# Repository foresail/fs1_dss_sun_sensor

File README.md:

# Foresail-1 DSS Sun Sensor

This repository contains the public available design files for the DSS sun sensor designed for the Foresail-1 Cubesat.

The performance and testing of this sensor has been documented in [this article](https://doi.org/10.1016/j.asr.2026.01.083).

The general characteristics of sensor design are:
- Dimensions: 20.4 mm × 24.8 mm × 7 mm
- Mass: 4.4 grams
- Panel mountedable into 14x14 mm hole with two M2 screws.
- Electrical connection by soldering on the panel PCB or by harness.
- FOV: ~30 degrees, resolution: 0.027°, accuracy: ±0.008°
- Refresh rate up to 38 Hz. (Sampling time: 15 ms + communication overhead)
- Can provide following data products:
    - Raw current measurements
    - Point & intensity measurements
    - Sun vector & intensity measurements
    - Angles & intensity measurements
- I2C digital serial interface (hardware version 4)
- RS-485 digital interface (hardware version 5)
- Low power consumption < 4 mW when active
- Nominal operating voltage: 3.6 - 3.8V: Can be extened easily to 2.0 – 5.5 V.

## Documentation

- [Research Paper](https://doi.org/10.1016/j.asr.2026.01.083)
- [FS1 ADCS DSS Sun Sensor Design Document](docs/FS1p_ADCS_DSS_Digital_Sun_Sensor_Hardware_Design.pdf)
- [Version 4 schematic (I2C variant)](v4/dss_v4_schema.pdf)
- [Version 4 firmware source code](v4/fw)
- [Version 5 schematic (RS-485 variant)](v5/dss_v5_schema.pdf)
- [Version 5 firmware source code](v5/fw)
- [Calibration and test tools for PC](calibration)
- [Mechanical design files](mechanical)

## Licence

The design is licenced under [CERN Open Hardware Licence Version 2](LICENCE)

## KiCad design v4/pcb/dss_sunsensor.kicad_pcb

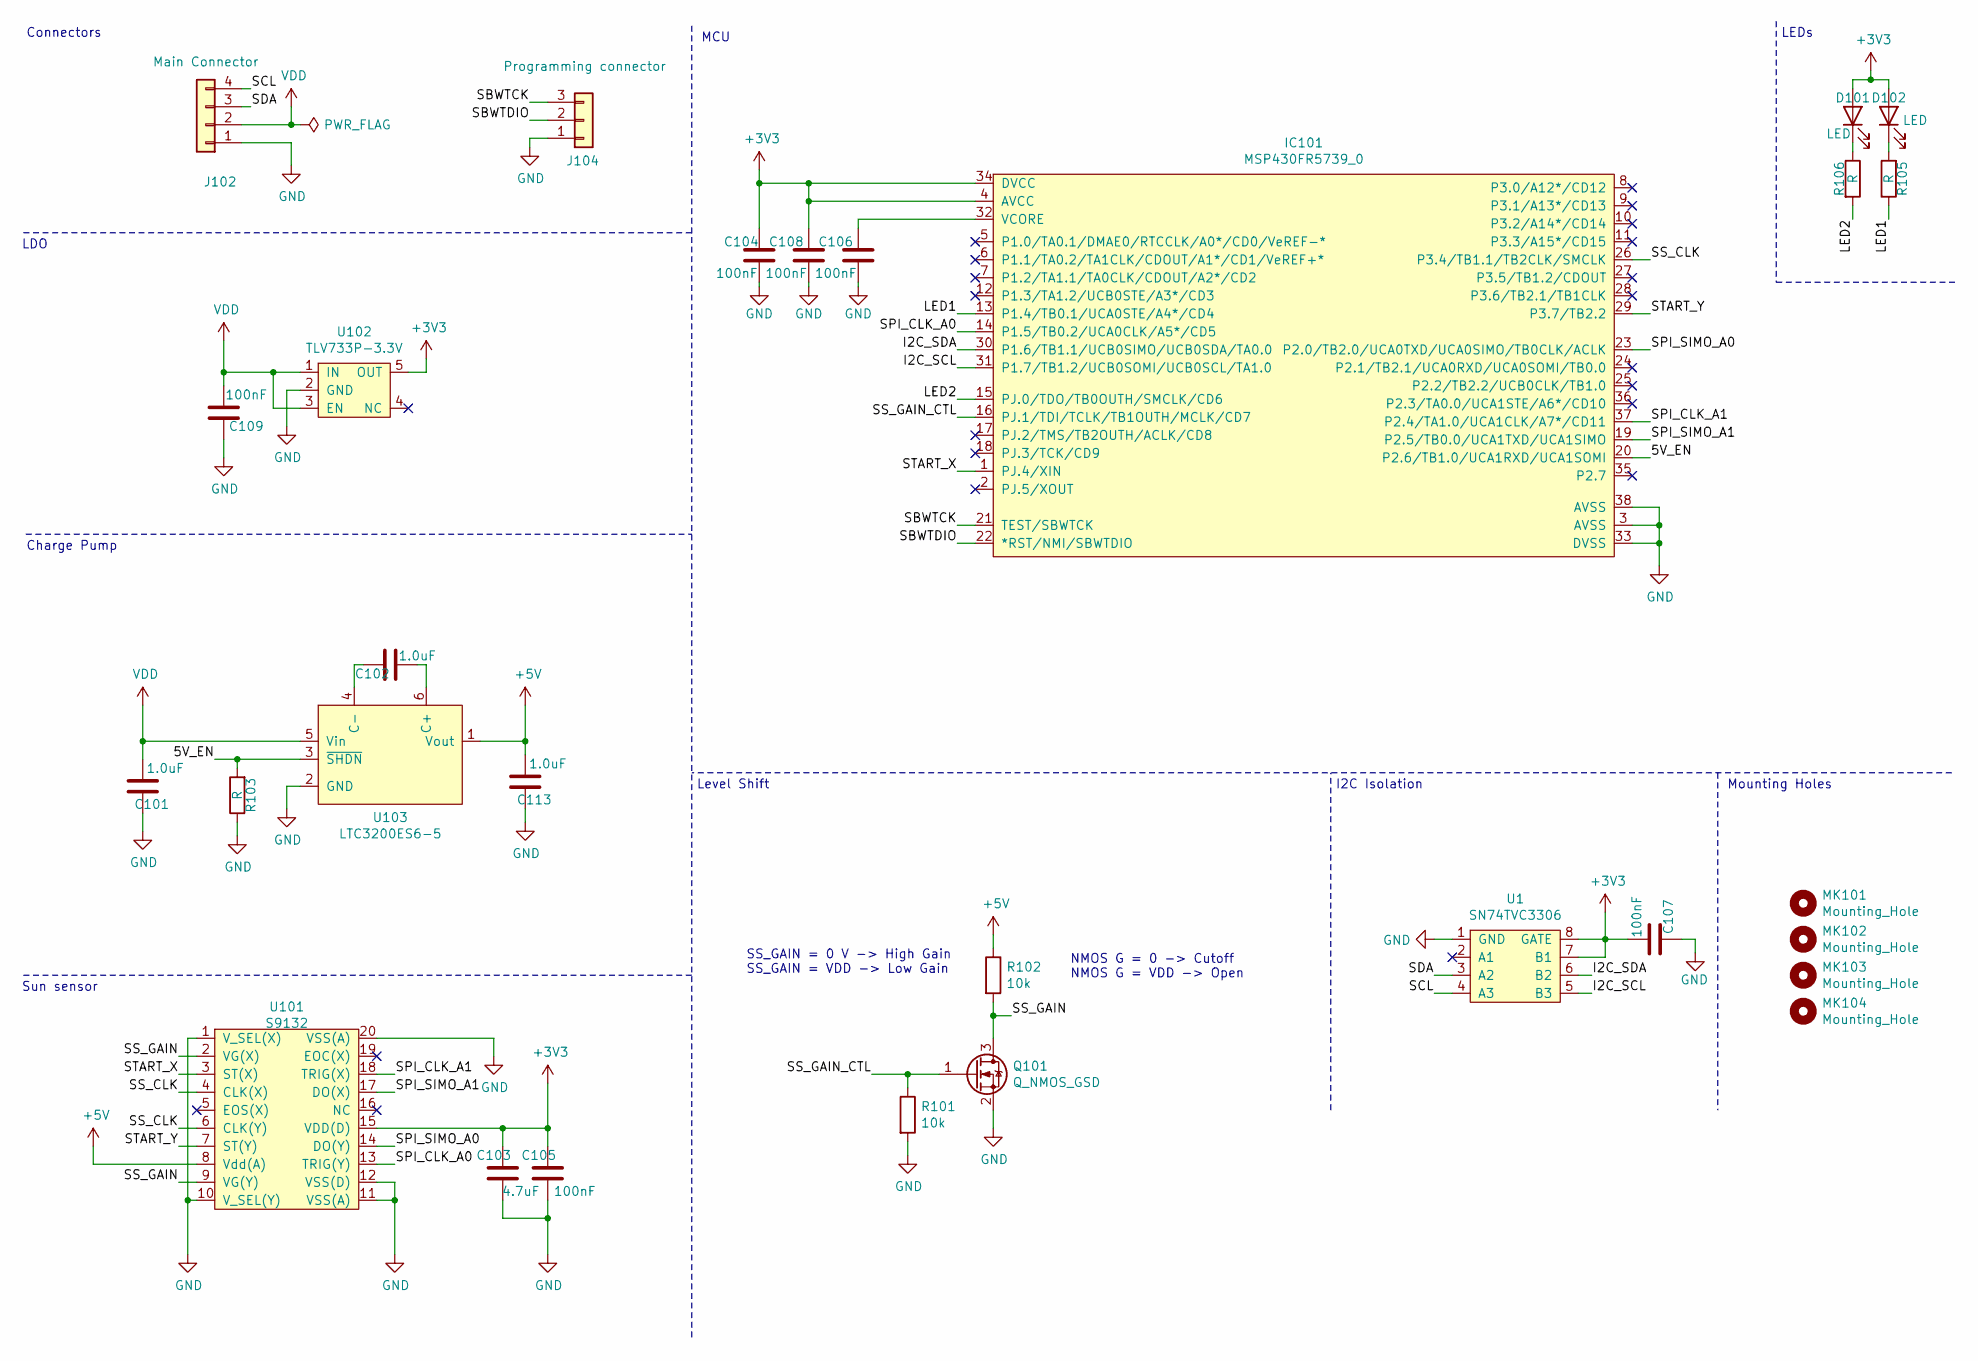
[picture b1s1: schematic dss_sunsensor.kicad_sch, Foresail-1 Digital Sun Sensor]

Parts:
C101, C102, C113: 1.0uF; C_0603_1608Metric
C103: 4.7uF; C_0603_1608Metric
C104, C105, C106, C107, C108, C109: 100nF; C_0402_1005Metric
D101, D102: LED; LED_0603_1608Metric
IC101: MSP430FR5739_0; TSSOP-38_6.1mm
J102: Main Connector; PinHeader_1x04_P1.27mm_Horizontal
J104: Programming connector; PinHeader_1x03_P1.27mm_Horizontal
MK101, MK102, MK103, MK104: Mounting_Hole; MountingHole_2.2mm_M2
Q101: Q_NMOS_GSD; SOT-23
R101, R102: 10k; R_0402_1005Metric
R103, R105, R106: R; R_0402_1005Metric
U1: SN74TVC3306; VSSOP-8_2.4x2.1mm_P0.5mm
U101: S9132
U102: TLV733P-3.3V; SOT-23-5
U103: LTC3200ES6-5; SOT-23-6

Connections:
+3V3: C103.2, C104.2, C105.2, C107.1, C108.2, D101.2 (A), D102.2 (A), IC101.4 (AVCC), IC101.34 (DVCC), U1.7 (B1), U1.8 (GATE), U101.15 (VDD(D)), U102.5 (OUT)
+5V: C113.1, R102.1, U101.8 (Vdd(A)), U103.1 (Vout)
/5V_EN: IC101.20 (P2.6/TB1.0/UCA1RXD/UCA1SOMI), R103.2, U103.3 (~SHDN)
/I2C_SCL: IC101.31 (P1.7/TB1.2/UCB0SOMI/UCB0SCL/TA1.0), U1.5 (B3)
/I2C_SDA: IC101.30 (P1.6/TB1.1/UCB0SIMO/UCB0SDA/TA0.0), U1.6 (B2)
/LED1: IC101.13 (P1.4/TB0.1/UCA0STE/A4*/CD4), R105.1
/LED2: IC101.15 (PJ.0/TDO/TB0OUTH/SMCLK/CD6), R106.2
/SBWTCK: IC101.21 (TEST/SBWTCK), J104.3
/SBWTDIO: IC101.22 (*RST/NMI/SBWTDIO), J104.2
/SCL: J102.4, U1.4 (A3)
/SDA: J102.3, U1.3 (A2)
/SPI_CLK_A0: IC101.14 (P1.5/TB0.2/UCA0CLK/A5*/CD5), U101.13 (TRIG(Y))
/SPI_CLK_A1: IC101.37 (P2.4/TA1.0/UCA1CLK/A7*/CD11), U101.18 (TRIG(X))
/SPI_SIMO_A0: IC101.23 (P2.0/TB2.0/UCA0TXD/UCA0SIMO/TB0CLK/ACLK), U101.14 (DO(Y))
/SPI_SIMO_A1: IC101.19 (P2.5/TB0.0/UCA1TXD/UCA1SIMO), U101.17 (DO(X))
/SS_CLK: IC101.26 (P3.4/TB1.1/TB2CLK/SMCLK), U101.4 (CLK(X)), U101.6 (CLK(Y))
/SS_GAIN: Q101.3 (D), R102.2, U101.2 (VG(X)), U101.9 (VG(Y))
/SS_GAIN_CTL: IC101.16 (PJ.1/TDI/TCLK/TB1OUTH/MCLK/CD7), Q101.1 (G), R101.1
/START_X: IC101.1 (PJ.4/XIN), U101.3 (ST(X))
/START_Y: IC101.29 (P3.7/TB2.2), U101.7 (ST(Y))
GND: C101.2, C103.1, C104.1, C105.1, C106.1, C107.2, C108.1, C109.2, C113.2, IC101.3 (AVSS), IC101.33 (DVSS), IC101.38 (AVSS), J102.1, J104.1, Q101.2 (S), R101.2, R103.1, U1.1 (GND), U101.1 (V_SEL(X)), U101.10 (V_SEL(Y)), U101.11 (VSS(A)), U101.12 (VSS(D)), U101.20 (VSS(A)), U102.2 (GND), U103.2 (GND)
unnamed: C102.1, U103.6 (C+)
unnamed: C102.2, U103.4 (C-)
unnamed: C106.2, IC101.32 (VCORE)
unnamed: D101.1 (K), R106.1
unnamed: D102.1 (K), R105.2
VDD: C101.1, C109.1, J102.2, U102.1 (IN), U102.3 (EN), U103.5 (Vin)

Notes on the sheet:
LDO
Mounting Holes
SS_GAIN = 0 V -> High Gain SS_GAIN = VDD -> Low Gain
Charge Pump
Sun sensor
NMOS G = 0 -> Cutoff NMOS G = VDD -> Open
Connectors
Level Shift
LEDs
MCU
I2C Isolation

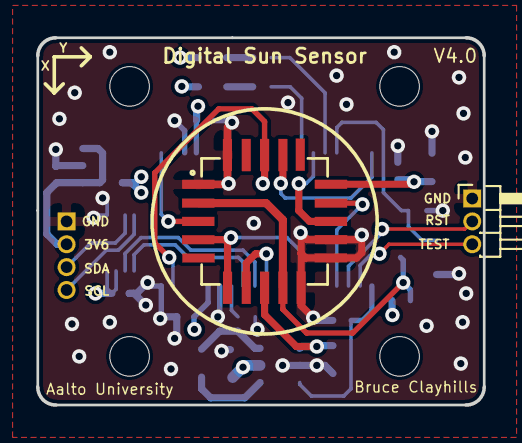
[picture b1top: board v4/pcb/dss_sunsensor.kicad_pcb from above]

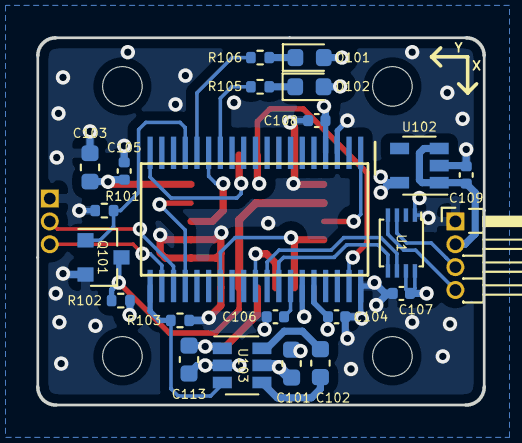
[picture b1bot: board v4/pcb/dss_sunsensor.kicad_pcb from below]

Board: 4 copper layers, 24.8 x 20.4 mm, 29 parts (23 on the bottom side), 27 nets.

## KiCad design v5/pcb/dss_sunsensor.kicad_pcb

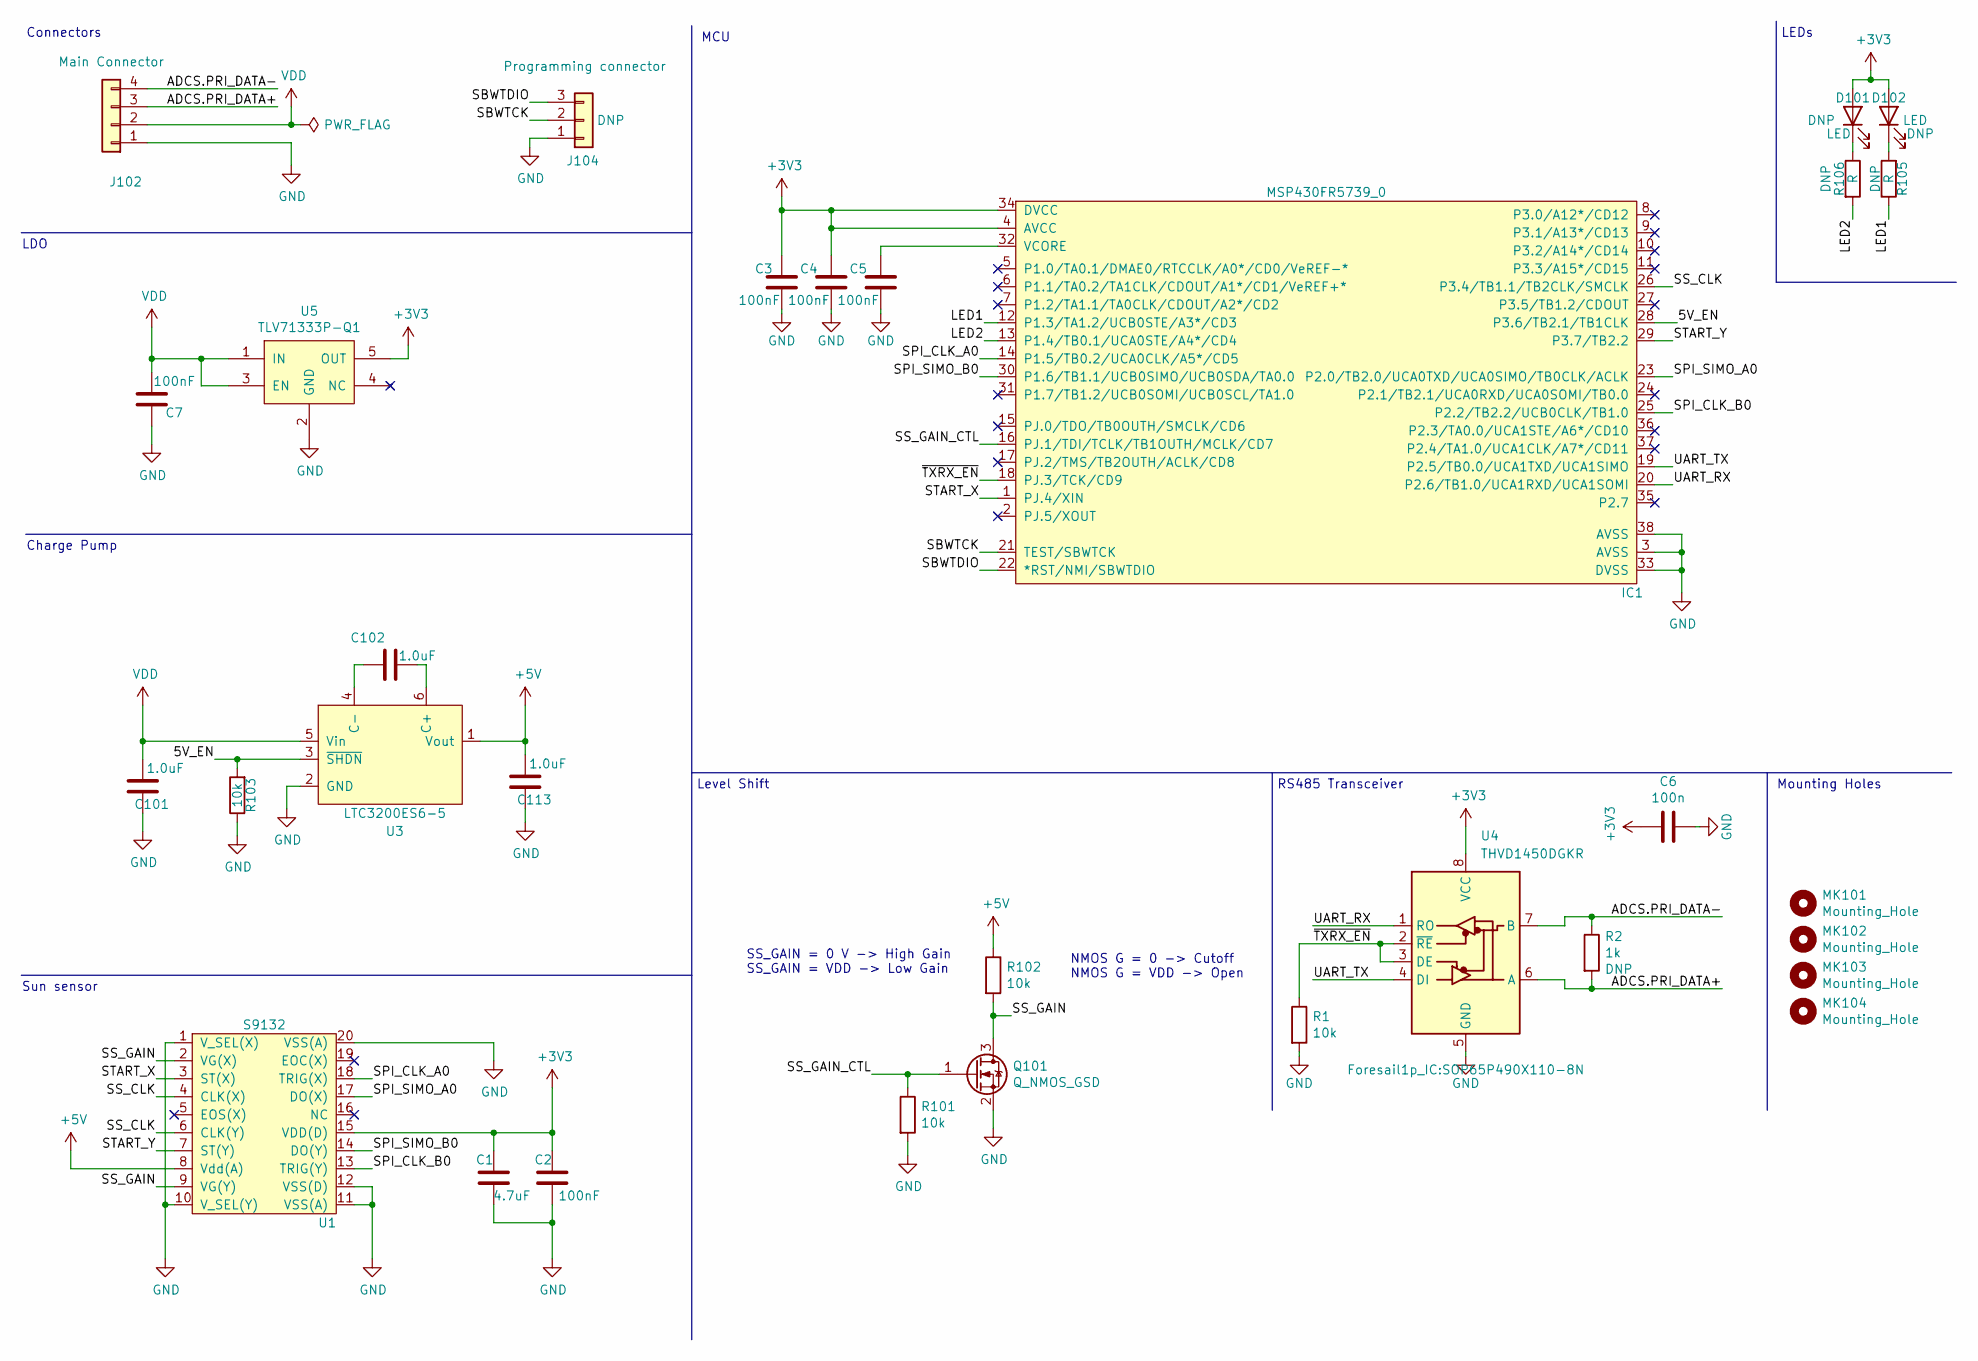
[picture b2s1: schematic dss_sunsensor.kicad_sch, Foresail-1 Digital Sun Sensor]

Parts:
C1: 4.7uF; C_0603_1608Metric
C2, C3, C4, C5, C7: 100nF; C_0402_1005Metric
C6: 100n; C_0402_1005Metric
C101, C102, C113: 1.0uF; C_0603_1608Metric
D101, D102: LED; LED_0603_1608Metric
IC1: MSP430FR5739_0; TSSOP-38_6.1mm
J102: Main Connector; PinHeader_1x04_P1.27mm_Horizontal
J104: Programming connector; PinHeader_1x03_P1.27mm_Horizontal
MK101, MK102, MK103, MK104: Mounting_Hole; MountingHole_2.2mm_M2
Q101: Q_NMOS_GSD; SOT-23
R1, R101, R102, R103: 10k; R_0402_1005Metric
R2: 1k; R_0402_1005Metric
R105, R106: R; R_0402_1005Metric
U1: S9132
U3: LTC3200ES6-5; SOT-23-6
U4: THVD1450DGKR; SOP65P490X110-8N
U5: TLV71333P-Q1; SOT-23-5; Mouser 595-TLV71333PQDBVRQ1

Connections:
+3V3: C1.2, C2.2, C3.2, C4.2, C6.1, D101.2 (A), D102.2 (A), IC1.4 (AVCC), IC1.34 (DVCC), U1.15 (VDD(D)), U4.8 (VCC), U5.5 (OUT); also elsewhere on the board
+5V: C113.1, R102.1, U1.8 (Vdd(A)), U3.1 (Vout)
/5V_EN: IC1.28 (P3.6/TB2.1/TB1CLK), R103.2, U3.3 (~SHDN)
/ADCS.PRI_DATA+: J102.3, R2.2, U4.6 (A)
/ADCS.PRI_DATA-: J102.4, R2.1, U4.7 (B)
/LED1: IC1.12 (P1.3/TA1.2/UCB0STE/A3*/CD3), R105.1
/LED2: IC1.13 (P1.4/TB0.1/UCA0STE/A4*/CD4), R106.2
/SBWTCK: IC1.21 (TEST/SBWTCK), J104.2
/SBWTDIO: IC1.22 (*RST/NMI/SBWTDIO), J104.3
/SPI_CLK_A0: IC1.14 (P1.5/TB0.2/UCA0CLK/A5*/CD5), U1.18 (TRIG(X))
/SPI_CLK_B0: IC1.25 (P2.2/TB2.2/UCB0CLK/TB1.0), U1.13 (TRIG(Y))
/SPI_SIMO_A0: IC1.23 (P2.0/TB2.0/UCA0TXD/UCA0SIMO/TB0CLK/ACLK), U1.17 (DO(X))
/SPI_SIMO_B0: IC1.30 (P1.6/TB1.1/UCB0SIMO/UCB0SDA/TA0.0), U1.14 (DO(Y))
/SS_CLK: IC1.26 (P3.4/TB1.1/TB2CLK/SMCLK), U1.4 (CLK(X)), U1.6 (CLK(Y))
/SS_GAIN: Q101.3 (D), R102.2, U1.2 (VG(X)), U1.9 (VG(Y))
/SS_GAIN_CTL: IC1.16 (PJ.1/TDI/TCLK/TB1OUTH/MCLK/CD7), Q101.1 (G), R101.1
/START_X: IC1.1 (PJ.4/XIN), U1.3 (ST(X))
/START_Y: IC1.29 (P3.7/TB2.2), U1.7 (ST(Y))
/UART_RX: IC1.20 (P2.6/TB1.0/UCA1RXD/UCA1SOMI), U4.1 (RO)
/UART_TX: IC1.19 (P2.5/TB0.0/UCA1TXD/UCA1SIMO), U4.4 (DI)
/~TXRX_EN: IC1.18 (PJ.3/TCK/CD9), R1.1, U4.2 (~RE), U4.3 (DE)
GND: C1.1, C2.1, C3.1, C4.1, C5.1, C6.2, C7.2, C101.2, C113.2, IC1.3 (AVSS), IC1.33 (DVSS), IC1.38 (AVSS), J102.1, J104.1, Q101.2 (S), R1.2, R101.2, R103.1, U1.1 (V_SEL(X)), U1.10 (V_SEL(Y)), U1.11 (VSS(A)), U1.12 (VSS(D)), U1.20 (VSS(A)), U3.2 (GND), U4.5 (GND), U5.2 (GND); also elsewhere on the board
unnamed: D101.1 (K), R106.1
unnamed: D102.1 (K), R105.2
unnamed: C5.2, IC1.32 (VCORE)
unnamed: C102.1, U3.6 (C+)
unnamed: C102.2, U3.4 (C-)
VDD: C7.1, C101.1, J102.2, U3.5 (Vin), U5.1 (IN), U5.3 (EN); also elsewhere on the board

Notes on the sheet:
Charge Pump
Level Shift
LDO
Sun sensor
SS_GAIN = 0 V -> High Gain SS_GAIN = VDD -> Low Gain
MCU
Mounting Holes
Connectors
RS485 Transceiver
NMOS G = 0 -> Cutoff NMOS G = VDD -> Open
LEDs

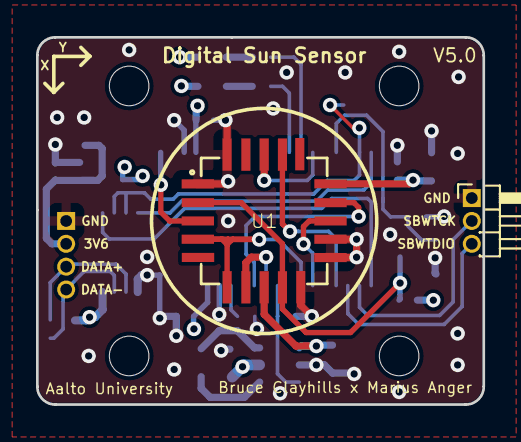
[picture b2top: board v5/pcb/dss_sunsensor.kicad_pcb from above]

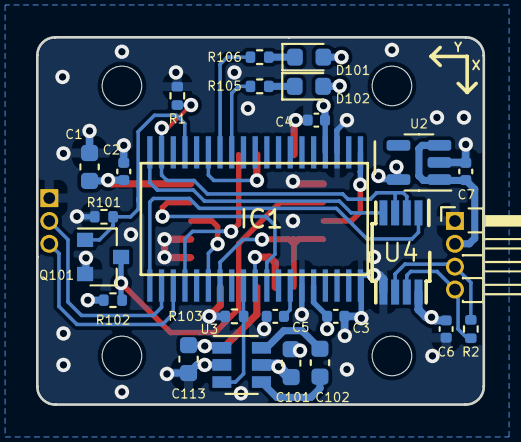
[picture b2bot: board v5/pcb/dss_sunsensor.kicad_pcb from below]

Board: 4 copper layers, 24.8 x 20.4 mm, 31 parts (25 on the bottom side), 28 nets.

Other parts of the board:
U2: TLV733P; SOT-23-5

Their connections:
+3V3: U2.5 (OUT); also elsewhere on the board
GND: U2.2 (GND); also elsewhere on the board
VDD: U2.1 (IN), U2.3 (EN); also elsewhere on the board

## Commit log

2025-03-05 pushed v4 and v5 similar to psd
2025-03-05 fixed readme
2025-04-14 dss orientation mistake
2026-03-24 Update README with performance article link
    Added a link to the performance and testing article for the DSS sun sensor.
